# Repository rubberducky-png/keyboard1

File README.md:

<center>

# rektek keyboard1: 81-Key Mechanical Keyboard

A fully custom 81-key mechanical keyboard designed by me, including the PCB, case, firmware, and assembly. This project was built to learn the complete keyboard design process while creating a functional keyboard.

Funded With The Macondo Program

## Features

- Custom PCB designed from scratch
- Hot-swappable MX-compatible switches
- QMK firmware support
- Screw-in stabilizers
- 3D printed two-piece tray mount case
- 8° typing angle for improved ergonomics
- bluetooth capabilites (connect to another screen while plugged into one)
  
## Why I Built It

I've always been interested in how things work, so when I was looking for a project I happened to glance at my hands, with my keyboard right underneath. Instead of buying an existing keyboard, I decided to design every  component like the PCB myself.

## Design Process

The project began by selecting a 81-key layout that has a lot of function but is also on the smaller side. I then designed the PCB in KiCad, routed all the traces, and added support for hot-swap sockets and USB-C connectivity. After the electronics were complete I designed a simple tray mount in Onshape. The case is made out of two PLA printed pieces and includes a 7° typing angle for a more comfortable typing experience. Because of small bed size I will have to print them in pieces.

Finally, the keyboard is programmed using qmk firmware.

## Challenges

Some of the biggest challenges included:

- Learning PCB routing and keyboard matrix design
- Designing a printable case that was able to support the pcb well
- Ensuring all mounting points aligned correctly

## Files:
I apologize for the mess, when I put my files into folders the larger ones kept deleting themselves.

## Images and Renders!

### Matrix Schematic

### OnShape Render

#### Case

### PCB

### Assembly

I apologize again for the semi-completed assembly, my document on Onshape couldn't take all of the lag from the amount of parts and started to kick me off of the document every time I went to import something.

## Sketch

## Bill of Materials (BOM)

| # | Component | Qty. | Cost |
|---:|---|---:|---:|
| 1 | Gateron Milky Yellow Pro Switches | 90 | $28.00 |
| 2 | 1N4148 Diodes | 82 | $2.46 |
| 3 | Cherry-style Stabilizer Set | 1 | $6.00 |
| 4 | ALPS EC11E Rotary Encoder | 1 | $2.75 |
| 5 | Raspberry Pi Pico | 1 | $3.95 |
| 6 | RN4871U-V/RM118 Bluetooth Module | 1 | $7.65 |
| 7 | 0805 Resistors | 2 | $0.04 |
| 8 | 0603 100nF Capacitor | 1 | $0.02 |
| 9 | 0805 Status LED | 1 | $0.05 |
| 10 | M2 Case Screws | 12 | $1.20 |
| 11 | M2 Heat-Set Inserts | 4 | $0.60 |
| 12 | JLCPCB PCB Fabrication | 5 | $27.20 |
| 13 | Glorious GPBT Basics Keycaps | 1 | $17.49 |
| 14 | USB-C to Micro-USB Cable | 1 | $6.00 |
| 15 | PETG/PLA Filament | 1 | $12.00 |
| 16 | JLCPCB DHL Express Shipping | 1 | $27.96 |
| | **Total** | | **$144.42** |
btw I also dont have a soldering iron but Im hoping I have enough fruits to get the pinecil

## Shoutout hackclub and the macondo program

</center>

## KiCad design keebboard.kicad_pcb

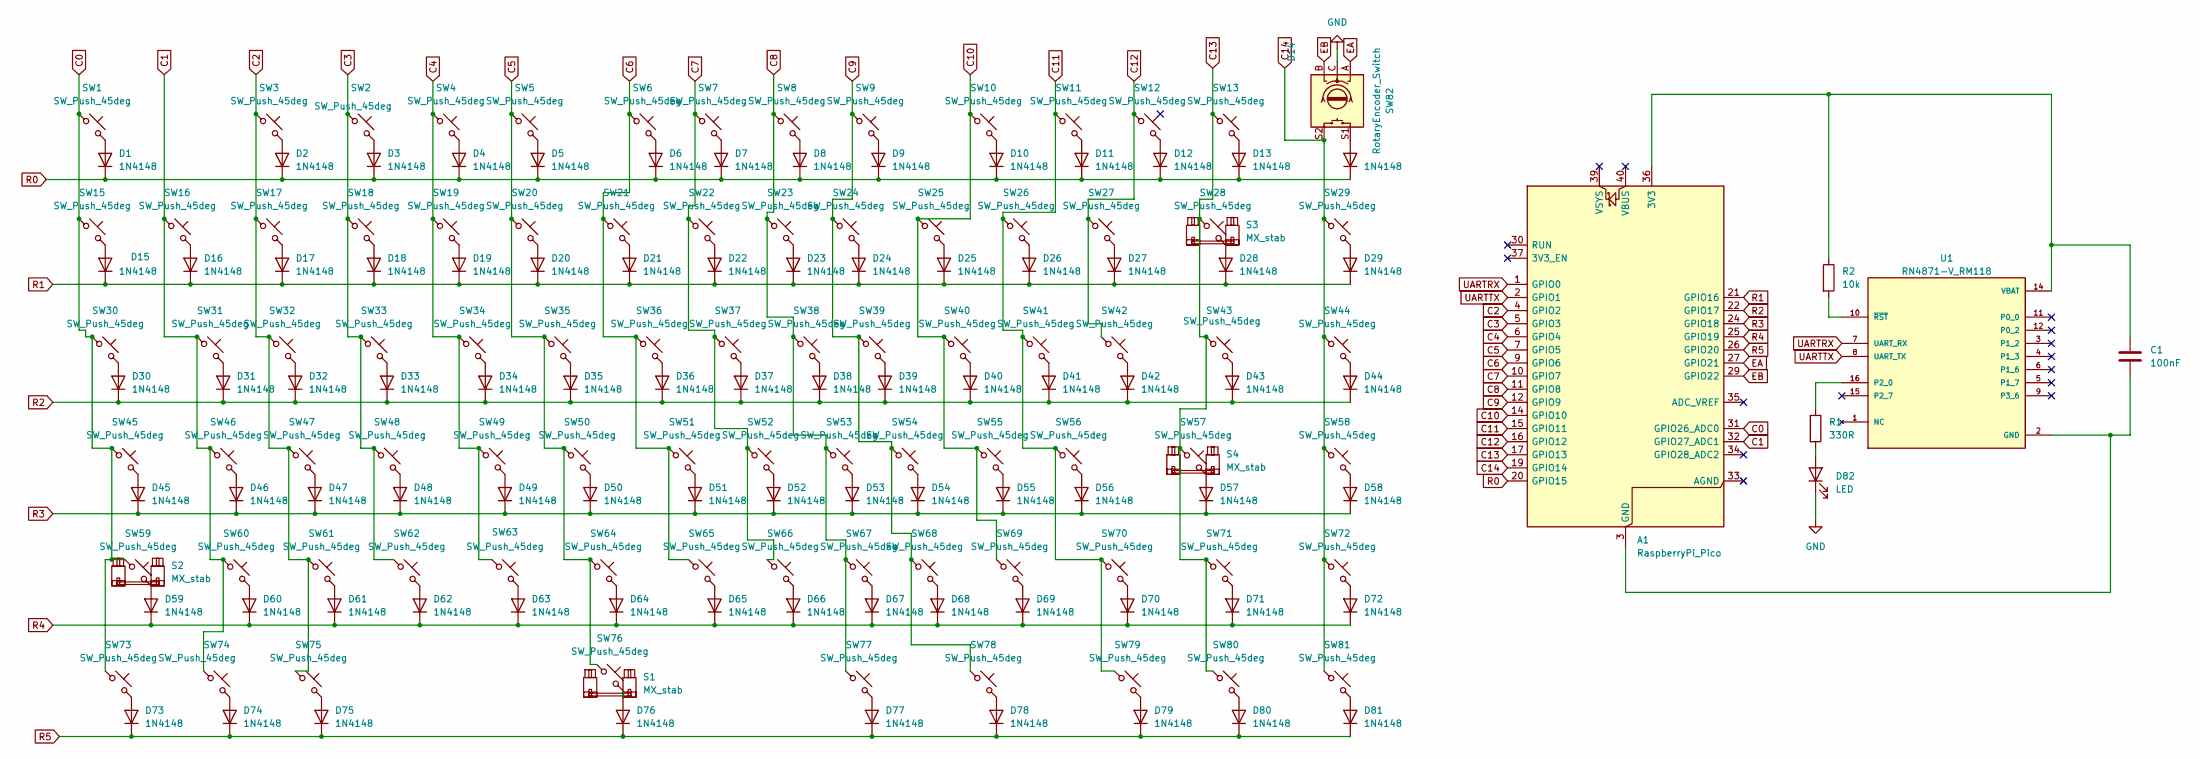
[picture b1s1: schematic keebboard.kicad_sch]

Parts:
A1: RaspberryPi_Pico; RaspberryPi_Pico_Common_Unspecified
C1: 100nF; C_0603_1608Metric_Pad1.08x0.95mm_HandSolder
D1, D2, D3, D4, D5, D6, D7, D8, D9, D10, D11, D12, D13, D14, D15, D16, D17, D18, D19, D20, D21, D22, D23, D24, D25, D26, D27, D28, D29, D30, D31, D32, D33, D34, D35, D36, D37, D38, D39, D40, D41, D42, D43, D44, D45, D46, D47, D48, D49, D50, D51, D52, D53, D54, D55, D56, D57, D58, D59, D60, D61, D62, D63, D64, D65, D66, D67, D68, D69, D70, D71, D72, D73, D74, D75, D76, D77, D78, D79, D80, D81: 1N4148; D_DO-35_SOD27_P7.62mm_Horizontal
D82: LED; LED_0805_2012Metric
R1: 330R; R_0805_2012Metric
R2: 10k; R_0805_2012Metric
S1, S2, S3, S4: MX_stab; STAB_MX_P_6.25u
SW1, SW2, SW3, SW4, SW5, SW6, SW7, SW8, SW9, SW10, SW11, SW12, SW13, SW15, SW16, SW17, SW18, SW19, SW20, SW21, SW22, SW23, SW24, SW25, SW26, SW27, SW29, SW31, SW32, SW33, SW34, SW35, SW36, SW37, SW38, SW39, SW40, SW41, SW42, SW44, SW46, SW47, SW48, SW49, SW50, SW51, SW52, SW53, SW54, SW55, SW56, SW58, SW60, SW61, SW62, SW63, SW64, SW65, SW66, SW67, SW68, SW69, SW71, SW72, SW79, SW80, SW81: SW_Push_45deg; SW_Cherry_MX_1.00u_PCB
SW28: SW_Push_45deg; SW_Cherry_MX_2.00u_PCB
SW30, SW78: SW_Push_45deg; SW_Cherry_MX_1.50u_PCB
SW43, SW45, SW70: SW_Push_45deg; SW_Cherry_MX_1.75u_PCB
SW57, SW59: SW_Push_45deg; SW_Cherry_MX_2.25u_PCB
SW73, SW74, SW75, SW77: SW_Push_45deg; SW_Cherry_MX_1.25u_PCB
SW76: SW_Push_45deg; SW_Cherry_MX_6.25u_PCB
SW82: RotaryEncoder_Switch; RotaryEncoder_Alps_EC11E-Switch_Vertical_H20mm
U1: RN4871-V_RM118; XCVR_RN4871-V_RM118; PARTREV E

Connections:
C0: A1.31 (GPIO26_ADC0), SW1.1, SW15.1, SW30.1, SW45.1, SW59.1, SW73.1
C1: A1.32 (GPIO27_ADC1), SW16.1, SW31.1, SW46.1, SW60.1, SW74.1
C2: A1.4 (GPIO2), SW3.1, SW17.1, SW32.1, SW47.1, SW61.1, SW75.1
C3: A1.5 (GPIO3), SW2.1, SW18.1, SW33.1, SW48.1, SW62.1
C4: A1.6 (GPIO4), SW4.1, SW19.1, SW34.1, SW49.1, SW63.1
C5: A1.7 (GPIO5), SW5.1, SW20.1, SW35.1, SW50.1, SW64.1, SW76.1
C6: A1.9 (GPIO6), SW6.1, SW21.1, SW36.1, SW51.1, SW65.1
C7: A1.10 (GPIO7), SW7.1, SW22.1, SW37.1, SW52.1, SW66.1
C8: A1.11 (GPIO8), SW8.1, SW23.1, SW38.1, SW53.1, SW67.1, SW77.1
C9: A1.12 (GPIO9), SW9.1, SW24.1, SW39.1, SW54.1, SW68.1, SW78.1
C10: A1.14 (GPIO10), SW10.1, SW25.1, SW40.1, SW55.1, SW69.1
C11: A1.15 (GPIO11), SW11.1, SW26.1, SW41.1, SW56.1, SW70.1, SW79.1
C12: A1.16 (GPIO12), SW12.1, SW27.1, SW42.1
C13: A1.17 (GPIO13), SW13.1, SW28.1, SW43.1, SW57.1, SW71.1, SW80.1
C14: A1.19 (GPIO14), SW29.1, SW44.1, SW58.1, SW72.1, SW81.1, SW82.S2
EA: A1.27 (GPIO21), SW82.A
EB: A1.29 (GPIO22), SW82.B
unnamed: A1.36 (3V3), C1.1, R2.1, U1.14 (VBAT)
unnamed: D1.2 (A), SW1.2
unnamed: D2.2 (A), SW3.2
unnamed: D3.2 (A), SW2.2
unnamed: D4.2 (A), SW4.2
unnamed: D5.2 (A), SW5.2
unnamed: D6.2 (A), SW6.2
unnamed: D7.2 (A), SW7.2
unnamed: D8.2 (A), SW8.2
unnamed: D9.2 (A), SW9.2
unnamed: D10.2 (A), SW10.2
unnamed: D11.2 (A), SW11.2
unnamed: D12.2 (A), SW12.2
unnamed: D13.2 (A), SW13.2
unnamed: D14.2 (A), SW82.S1
unnamed: D15.2 (A), SW15.2
unnamed: D16.2 (A), SW16.2
unnamed: D17.2 (A), SW17.2
unnamed: D18.2 (A), SW18.2
unnamed: D19.2 (A), SW19.2
unnamed: D20.2 (A), SW20.2
unnamed: D21.2 (A), SW21.2
unnamed: D22.2 (A), SW22.2
unnamed: D23.2 (A), SW23.2
unnamed: D24.2 (A), SW24.2
unnamed: D25.2 (A), SW25.2
unnamed: D26.2 (A), SW26.2
unnamed: D27.2 (A), SW27.2
unnamed: D28.2 (A), SW28.2
unnamed: D29.2 (A), SW29.2
unnamed: D30.2 (A), SW30.2
unnamed: D31.2 (A), SW31.2
unnamed: D32.2 (A), SW32.2
unnamed: D33.2 (A), SW33.2
unnamed: D34.2 (A), SW34.2
unnamed: D35.2 (A), SW35.2
unnamed: D36.2 (A), SW36.2
unnamed: D37.2 (A), SW37.2
unnamed: D38.2 (A), SW38.2
unnamed: D39.2 (A), SW39.2
unnamed: D40.2 (A), SW40.2
unnamed: D41.2 (A), SW41.2
unnamed: D42.2 (A), SW42.2
unnamed: D43.2 (A), SW43.2
unnamed: D44.2 (A), SW44.2
unnamed: D45.2 (A), SW45.2
unnamed: D46.2 (A), SW46.2
unnamed: D47.2 (A), SW47.2
unnamed: D48.2 (A), SW48.2
unnamed: D49.2 (A), SW49.2
unnamed: D50.2 (A), SW50.2
unnamed: D51.2 (A), SW51.2
unnamed: D52.2 (A), SW52.2
unnamed: D53.2 (A), SW53.2
unnamed: D54.2 (A), SW54.2
unnamed: D55.2 (A), SW55.2
unnamed: D56.2 (A), SW56.2
unnamed: D57.2 (A), SW57.2
unnamed: D58.2 (A), SW58.2
unnamed: D59.2 (A), SW59.2
unnamed: D60.2 (A), SW60.2
unnamed: D61.2 (A), SW61.2
unnamed: D62.2 (A), SW62.2
unnamed: D63.2 (A), SW63.2
unnamed: D64.2 (A), SW64.2
unnamed: D65.2 (A), SW65.2
unnamed: D66.2 (A), SW66.2
unnamed: D67.2 (A), SW67.2
unnamed: D68.2 (A), SW68.2
unnamed: D69.2 (A), SW69.2
unnamed: D70.2 (A), SW70.2
unnamed: D71.2 (A), SW71.2
unnamed: D72.2 (A), SW72.2
unnamed: D73.2 (A), SW73.2
unnamed: D74.2 (A), SW74.2
unnamed: D75.2 (A), SW75.2
unnamed: D76.2 (A), SW76.2
unnamed: D77.2 (A), SW77.2
unnamed: D78.2 (A), SW78.2
unnamed: D79.2 (A), SW79.2
unnamed: D80.2 (A), SW80.2
unnamed: D81.2 (A), SW81.2
unnamed: D82.2 (A), R1.2
unnamed: R1.1, U1.16 (P2_0)
unnamed: R2.2, U1.10 (~RST)
R0: A1.20 (GPIO15), D1.1 (K), D2.1 (K), D3.1 (K), D4.1 (K), D5.1 (K), D6.1 (K), D7.1 (K), D8.1 (K), D9.1 (K), D10.1 (K), D11.1 (K), D12.1 (K), D13.1 (K), D14.1 (K)
R1: A1.21 (GPIO16), D15.1 (K), D16.1 (K), D17.1 (K), D18.1 (K), D19.1 (K), D20.1 (K), D21.1 (K), D22.1 (K), D23.1 (K), D24.1 (K), D25.1 (K), D26.1 (K), D27.1 (K), D28.1 (K), D29.1 (K)
R2: A1.22 (GPIO17), D30.1 (K), D31.1 (K), D32.1 (K), D33.1 (K), D34.1 (K), D35.1 (K), D36.1 (K), D37.1 (K), D38.1 (K), D39.1 (K), D40.1 (K), D41.1 (K), D42.1 (K), D43.1 (K), D44.1 (K)
R3: A1.24 (GPIO18), D45.1 (K), D46.1 (K), D47.1 (K), D48.1 (K), D49.1 (K), D50.1 (K), D51.1 (K), D52.1 (K), D53.1 (K), D54.1 (K), D55.1 (K), D56.1 (K), D57.1 (K), D58.1 (K)
R4: A1.25 (GPIO19), D59.1 (K), D60.1 (K), D61.1 (K), D62.1 (K), D63.1 (K), D64.1 (K), D65.1 (K), D66.1 (K), D67.1 (K), D68.1 (K), D69.1 (K), D70.1 (K), D71.1 (K), D72.1 (K)
R5: A1.26 (GPIO20), D73.1 (K), D74.1 (K), D75.1 (K), D76.1 (K), D77.1 (K), D78.1 (K), D79.1 (K), D80.1 (K), D81.1 (K)
UARTRX: A1.1 (GPIO0), U1.7 (UART_RX)
UARTTX: A1.2 (GPIO1), U1.8 (UART_TX)

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
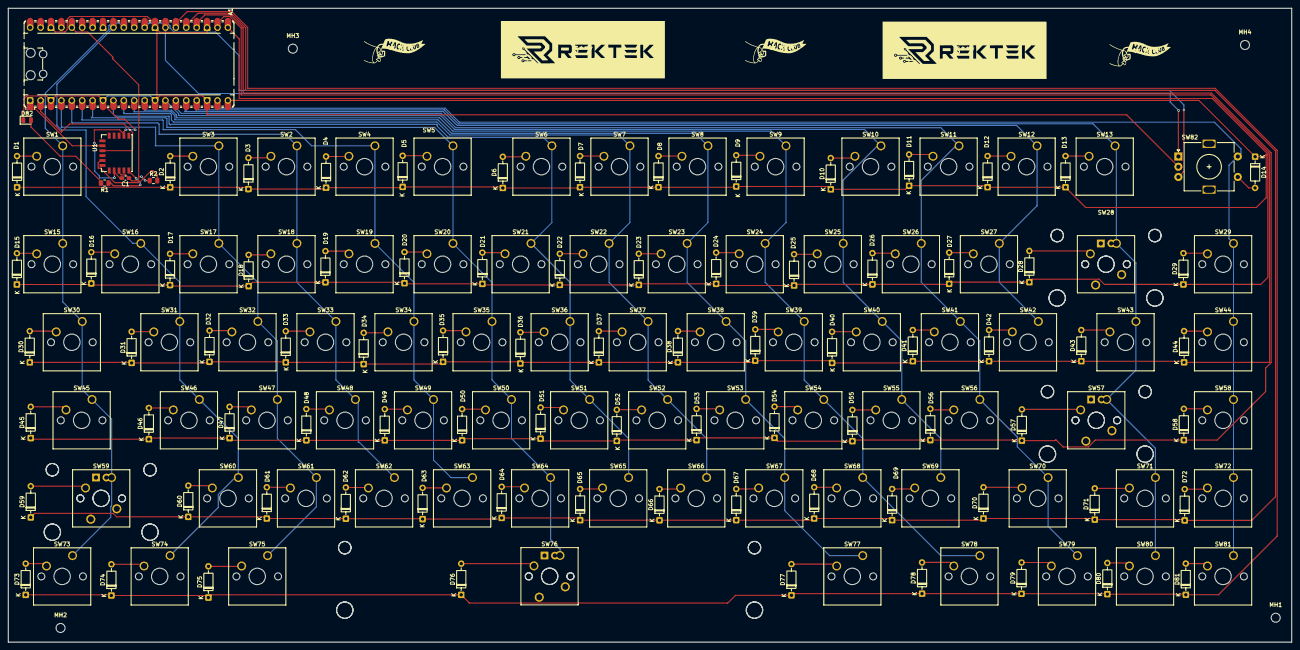
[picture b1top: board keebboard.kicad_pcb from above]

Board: 2 copper layers, 313.2 x 154.7 mm, 176 parts (0 on the bottom side), 111 nets.

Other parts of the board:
MH1, MH2, MH3, MH4: MountingHole_2.2mm_M2
